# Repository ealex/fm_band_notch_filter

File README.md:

# fm_band_notch_filter
FM band notch filter
Designed to block 80-108MHz 
Designed using https://rf-tools.com/lc-filter/

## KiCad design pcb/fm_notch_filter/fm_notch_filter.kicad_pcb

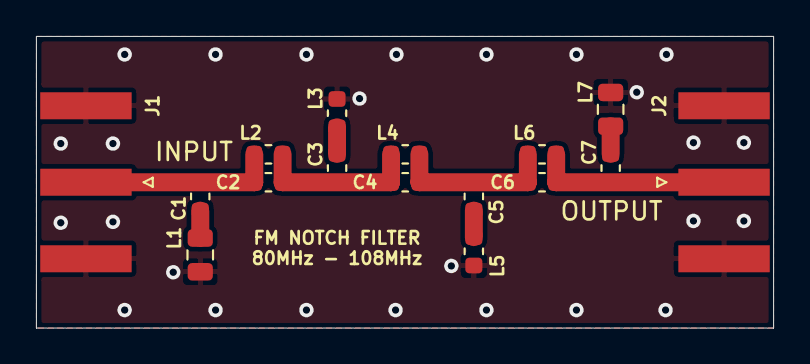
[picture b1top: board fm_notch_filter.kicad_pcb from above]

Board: 2 copper layers, 41.0 x 16.2 mm, 16 parts (0 on the bottom side), 9 nets.

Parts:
C1, C7: 12p; C_0603_1608Metric
C2, C6: 82p; C_0603_1608Metric
C3, C5: 22p; C_0603_1608Metric
C4: 75p; C_0603_1608Metric
J1, J2: Conn_Coaxial; SMA_Amphenol_132289_EdgeMount
L1, L7: 240n; L_0805_2012Metric
L2, L6: 36n; L_0603_1608Metric
L3, L5: 130n; L_0603_1608Metric
L4: 39n; L_0603_1608Metric

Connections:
GND: J1.2, J2.2, L1.2, L3.2, L5.2, L7.2
unnamed: C1.1, C2.2, J1.1, L2.1
unnamed: C1.2, L1.1
unnamed: C2.1, C3.1, C4.2, L2.2, L4.1
unnamed: C3.2, L3.1
unnamed: C4.1, C5.1, C6.2, L4.2, L6.1
unnamed: C5.2, L5.1
unnamed: C6.1, C7.1, J2.1, L6.2
unnamed: C7.2, L7.1

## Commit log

2022-03-30 add design tool parameters
2022-04-05 update design files, add Farnell shopping card
2022-04-09 schematic and pcb
